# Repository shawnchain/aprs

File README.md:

# TinyAPRS - A cheap APRS TNC for HAM #

### What is TinyAPRS ###

Like most of the APRS TNCs, TinyAPRS is an AFSK1200 modem that decodes radio signals into AX25 data packets. TinyAPRS also supports KISS protocol, so you can use it with most of the APRS applications.

Unlike most of the APRS TNCs, tinyAPRS is VERY VERY CHEAP. It will only cost $10 to build one. That means you can build your own APRS IGATE or tracking beacon with very low cost.

TinyAPRS has good performance on decoding. 
Currently, it works perfectly with my GM300 radio and decodes packets successfully from OT++(The local Digipeater)/FTM350R(My Car) and other devices. Based on my test, it decodes 850+ records from WA8LMF APRS TestCD/Track1. 

### How did it work ###

TinyAPRS is built on the giants shoulder.

 - An ALC/Filter circut that is the same as OpenTracker used, which will  greatly improve the decode capability.(Thank you to BH4TDV for sharing the circut design)
 - A fine-tunned AFSK/AX25/KISS stack that runs on AVR chip with very small memory footprints. (Thank you to Mark Qvist for his MicroAPRS, but mine now is better :)
 - Good abstraction to the hardware with BertOS, which made it easy to port TinyAPRS firmware to other MCUs.

Technical specification 

 - Main Chip : ATMEL/ATMEGA328P (Cheap clones of Arduino ProMini, could be ported to other type of AVR MCUs with ease)
 - ALC circut: MCP6001 OPA
 - Firmware  : AFSK1200/KISS(P-CSMA)/AT Serial

### The License ###

TinyAPRS is released under GPL license, **but with the following restriction** :

 - Any person, who decide to use and/or get benefits from any part of the TinyAPRS project, will be obliged to send the author(me/BG5HHP/Shawn) a gift. (Any kind of gift will be fine but Beers/PostCards/Parts of HAM radios are preferred :)
 - No commercial use.
 - All GPL restrictions

### Pictures ###

Please visit my [weibo album](http://www.weibo.com/p/1005052321043580/album?from=page_100505&mod=TAB#place "Weibo Album") for more pictures.

Cheers,

Shawn (BG5HHP)

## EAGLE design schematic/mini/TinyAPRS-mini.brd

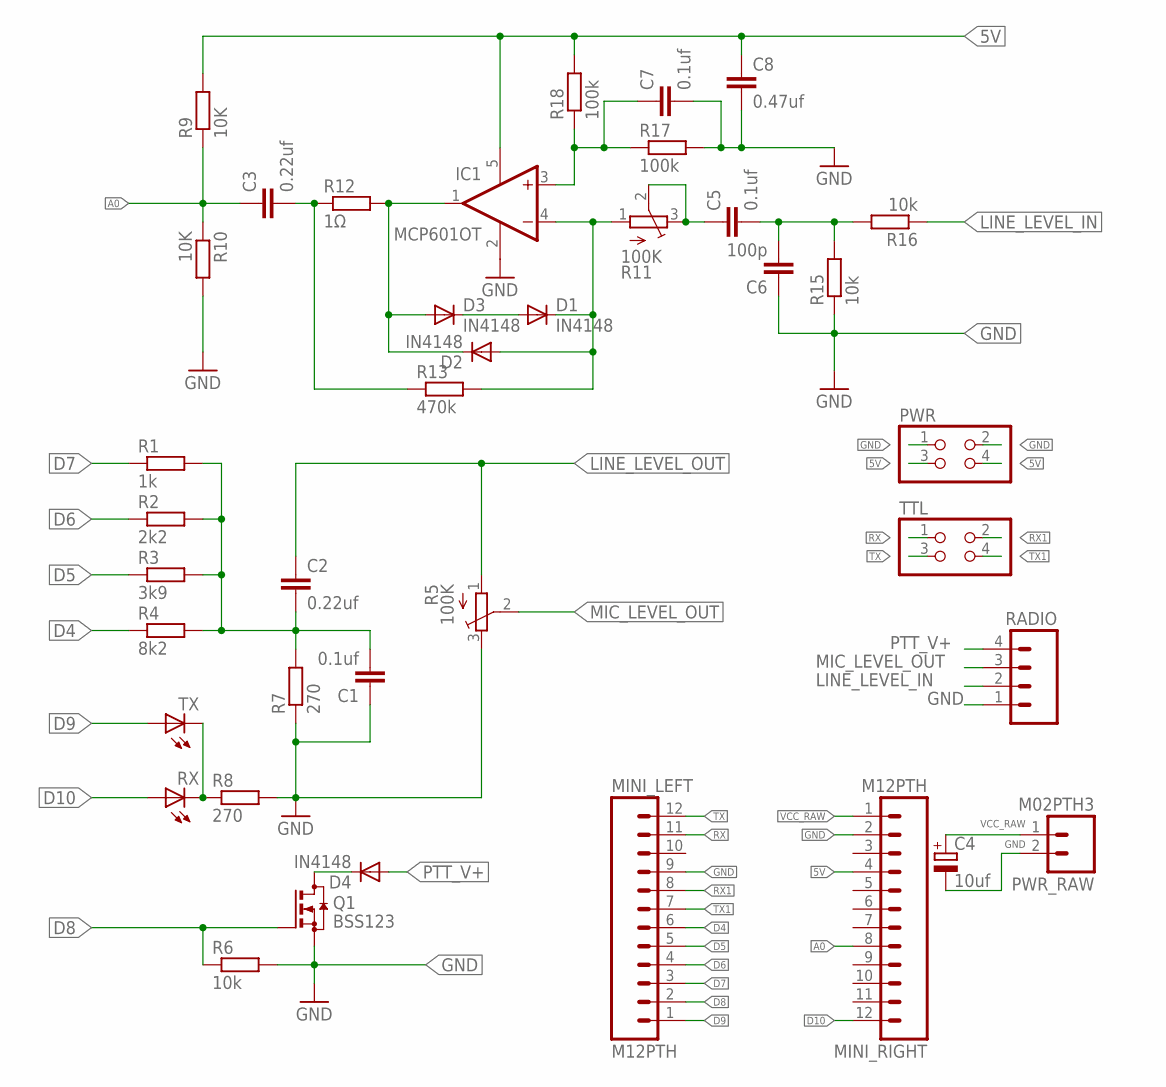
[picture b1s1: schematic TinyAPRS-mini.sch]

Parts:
C1, C5, C7: 0.1uf; C050-024X044
C2, C3: 0.22uf; C050-024X044
C4: 10uf; E2,5-5
C6: 100p; C050-024X044
C8: 0.47uf; C050-024X044
D1, D2, D3, D4: IN4148; D-2.5
IC1: MCP601OT; SOT23-5
MINI_LEFT: M12PTH; 1X12
MINI_RIGHT: M12PTH; 1X12
PWR: PINHD-2X2; 2X02
PWR_RAW: M02PTH3; 1X02_LONGPADS
Q1: BSS123; SOT23
R1: 1k; 0204/5
R2: 2k2; 0204/5
R3: 3k9; 0204/5
R4: 8k2; 0204/5
R5, R11: 100K; TC33X
R6, R15, R16: 10k; 0204/5
R7: 270; 0204/5
R8: 270; 0204V
R9, R10: 10K; 0204/5
R12: 1Ω; 0204V
R13: 470k; 0204/5
R17, R18: 100k; 0204/5
RADIO: M04PTH; 1X04
RX: LED_ELD260; LED_LD260
TTL: PINHD-2X2; 2X02
TX: LED_ELD260; LED_LD260

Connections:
5V: C8.1, IC1.5 (V+), MINI_RIGHT.4, PWR.3, PWR.4, R9.2, R18.2
A0: C3.1, MINI_RIGHT.8, R9.1, R10.1
D4: MINI_LEFT.6, R4.1
D5: MINI_LEFT.5, R3.1
D6: MINI_LEFT.4, R2.1
D7: MINI_LEFT.3, R1.1
D8: MINI_LEFT.2, Q1.1 (G), R6.1
D9: MINI_LEFT.1, TX.A
D10: MINI_RIGHT.12, RX.A
GND: C1.1, C4.-, C6.1, C7.2, C8.2, IC1.2 (V-), MINI_LEFT.9, MINI_RIGHT.2, PWR.1, PWR.2, PWR_RAW.2, Q1.2 (S), R5.3 (E), R6.2, R7.1, R8.2, R10.2, R15.1, R17.2, RADIO.1
LINE_LEVEL_IN: R16.1, RADIO.2
LINE_LEVEL_OUT: C2.1, R5.1 (A)
MIC_LEVEL_OUT: R5.2 (S), RADIO.3
unnamed: R8.1, RX.K (C), TX.K (C)
unnamed: D2.C, D3.A, IC1.1 (OUT), R12.2
unnamed: D1.C, D2.A, IC1.4 (-IN), R11.1 (A), R13.2
unnamed: D4.C, Q1.3 (D)
unnamed: C5.1, R11.2 (S), R11.3 (E)
unnamed: C5.2, C6.2, R15.2, R16.2
unnamed: C7.1, IC1.3 (+IN), R17.1, R18.1
unnamed: D1.A, D3.C
unnamed: C3.2, R12.1, R13.1
PTT_V+: D4.A, RADIO.4
RX: MINI_LEFT.11, TTL.1
RX1: MINI_LEFT.8, TTL.2
R_DAC: C1.2, C2.2, R1.2, R2.2, R3.2, R4.2, R7.2
TX: MINI_LEFT.12, TTL.3
TX1: MINI_LEFT.7, TTL.4
VCC_RAW: C4.+, MINI_RIGHT.1, PWR_RAW.1

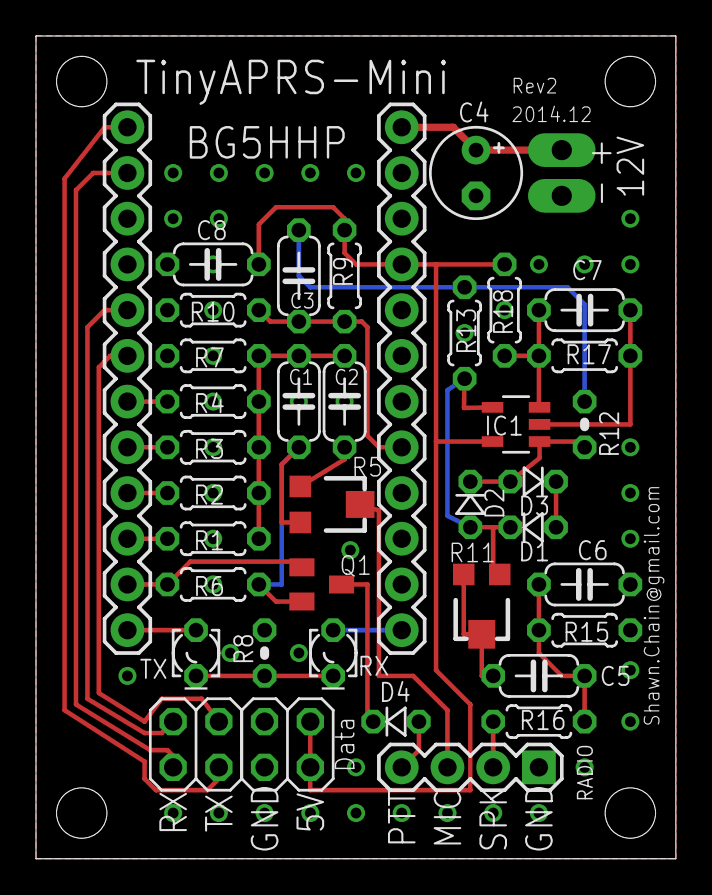
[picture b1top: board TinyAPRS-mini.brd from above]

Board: 2 copper layers, 35.5 x 45.7 mm, 39 parts (0 on the bottom side), 29 nets.

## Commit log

2014-10-11 Add MicroAPRS2 source code
2014-10-13 Updated to use GPIO D8 for PTT, D9,D10 for TX,RX
2014-10-14 Add LCD4884 driver
2014-10-14 Add ATMEGA644PA CPU support to BeRTOS
2014-10-14 Add the missing cpu definition file
2014-10-18 Add HAL macros to LCD drv
2014-10-18 Add External AREF macros to AFSK drv
2014-10-18 Add LCD support to console module
2014-10-18 Console supports LCD
2014-10-21 Add CONFIG_KISS_QUEUE parameter for the kiss protocol
2014-11-25 Add ATMEGA644PA patch
2014-11-25 Add TinyAPRS project file
2014-11-25 Add TinyAPRS project
2015-02-07 Commit pending changes on MicroAPRS2 copy, now will work on TinyAPRS branch
2015-02-07 Add experimental KISS support
2015-02-07 move unchanged cfg headers to templates folder for better reading
2015-02-08 ax25 driver supports pass_through mode.
2015-02-11 disable KISS message queue when CONFIG_KISS_QUEUE=0 to save ram space.
2015-02-11 module configuration update.
2015-02-11 Simple AT command supported for callsign and ssid configuration.
2015-02-11 CSMA before sending even sending queue is disabled.
2015-02-13 Refactored to: extract beacon module; support KISS/COMMAND mode switch
2015-02-13 Kiss module now supports return command
2015-02-14 Increase the premble and trailer time for better decoding performance.
2015-02-14 Add beacon_send_test(uint8_t)
2015-02-14 update callsign and ssid from settings
2015-02-14 Optimize the path in test message.
2015-02-15 Adjust afsk premble and trail time. should be configurable.
2015-02-19 Suports print string from PROGMEM to save runtime ram
2015-02-19 The new console module for AT command support.
2015-02-19 Display free mem after init.
2015-02-20 Refactor KISS module to work with other modules that shares one UART
2015-02-20 Refactored console serial read
2015-02-21 Compatible with OT2/Other KISS enable command.
2015-02-24 Add configuration tool skeleton code
2015-02-28 Add print_size and flash target to the makefile
2015-02-28 Add settings support for MYCALL,DEST,PATH
2015-02-28 respond 'INVALID CMD VALUE' to console when command handler returns false
2015-02-28 Add console test command, use CONSOLE_TEST_COMMAND_ENABLED to enable/disable.
2015-02-28 settings copy call value optimized.
2015-03-01 Refactor the console and commands
2015-03-03 Clean up console commands.
2015-03-03 KISS module optimized.
2015-03-03 Beacon test message bugfix
2015-03-07 soft reboot device after settings are cleared.
2015-03-07 New console command supported: location and comments
2015-03-07 Code clean up on console settings commands
2015-03-07 Help command clean up.
2015-03-07 restore the changes on main.c
2015-03-07 console help command clean up
2015-03-08 don't print ssid 0
2015-03-08 print received ax25 message in TNC2-stye format in normal mode.
2015-03-08 Ready for 1.0-RC
2015-03-15 Add initial soft_serial code
2015-03-15 tesing soft_serial
2015-03-15 Add missing hw_pins_arduino.h
2015-03-15 Disable soft reset by default
2015-03-15 Ready for 1.0
2015-03-15 Remove legacy codes
2015-03-15 README typo fix.
2015-03-15 For my bad english.
2015-03-15 Pictures!
2015-03-15 Update README with pictures.
2015-03-16 Add schematic for the mini board
2015-03-20 Heading for the 1.1
2015-03-20 Add .settings to ignore list
2015-03-20 softser code cleanup
2015-03-25 beacon module optimized.
2015-03-25 Optimized softser for the radio module initialization.
2015-03-25 radio modules is disabled by default on 328p
2015-03-25 rename utils module.
2015-03-25 code clean up
2015-03-25 Supports raw packet in settings, but disabled by default.
2015-03-25 console serial buf down to 32bytes if raw packet is disabled in settings to save sram space
2015-03-25 Remove PHGD/LOCATION/COMMENTS from settings.
2015-03-25 AT command parser bugfix
2015-03-25 Symbol in settings.
2015-03-25 symbol table and index support.
2015-03-26 beacon now reads the settings for raw aprs data
2015-03-26 reduce the afsk premble time to 350ms
2015-03-27 add doc folder
2015-03-27 Update doc
2015-03-27 Add gps nmea parser
2015-03-27 Add gps callback
2015-03-29 Extract the read_a_line logic into the reader class.
    Configure the serial in non-blocking mode by setting
    CONFIG_SER_RXTIMEOUT = 0
2015-03-29 Extract serial instance to global.
2015-03-29 Extract g_afsk & g_ax25 instances to global.
    KISS module now uses kfile_getc to read a char from serial, instead of
    the deprecated ser_getchar_nowait() call.
2015-03-29 Extract gps to global
2015-03-29 Rename NMEA to GPS
2015-03-30 gps module refactored
2015-03-30 modify ax25 to print message count when CONFIG_AX25_DEBUG_PRINT_MESSAGE_COUNT = 1
2015-03-30 supports tracker mode. currently use AT+MODE=2 to enable
2015-03-31 Beacon module refers GPS module directly.
2015-03-31 run_mode now will be saved to settings and device automatically enter even after reboot.
2015-03-31 beacon supports GPS tracking.
2015-03-31 check_run_mode bugfix in main loop
2015-03-31 cmd_help() text refined.
2015-03-31 always trigger send when first time gps location arrived.
2015-04-01 smart beacon
2015-04-01 always set gps baudrate to 9600
2015-04-01 beacon dst callsign bugfix
2015-04-01 dont pause when dumping beacon payload
2015-04-01 GPS initialize sequence optimized.
2015-04-02 increase the wait time of each gps init command
2015-04-02 Bugfix on GPS receiving.
2015-04-03 GPS works
2015-04-05 Bugfix on ax25_print() that missing message
2015-04-05 light on gps indicator LED inside gps mdoule.
2015-04-07 remove unused fields in struct Reader to save ram.
2015-04-07 KISS and CONSOLE now shares the same read buffer which will save 330 bytes of sram.
2015-04-07 KISS uses global afsk & ax25 handlers.
2015-04-07 Use CONFIG_AX25_FRAME_BUF_LEN as shared buffer length
2015-04-09 Collecting ax25 protocol statistic info.
2015-04-09 rename the beacon text in settings and changes the AT+TEXT, AT+CALL commands.
2015-04-09 Extract free_mem() into utils, which returns the free mem might be slightly smaller than the actuall one(2 bytes maybe) but fine.
2015-04-09 reader code clean up
2015-04-09 add BEACON_INTERVAL to settings
2015-04-09 Use AT+BEACON=45 to setup beacon broadcast interval.
2015-04-09 works with latest refactors.
2015-04-10 gps_get_location() now converts lat/lon in to decimal number from degress string. and other minor fixes on GPS modules.
2015-04-10 smart beacon implemented. simplified beacon test code.
2015-04-10 work with latest changes.
2015-04-10 GPS supports GPGGA sentence.
2015-04-10 convert altitude to feet for APRS payload.
2015-04-10 Fixed the GPS bug that failed to parse timestamp.
2015-04-11 Fix incorrect altitude in beacon comments.
2015-04-13 smartbeacon heading check bugfix.
2015-04-13 Bugfix that beacon send failure if text is blank.
2015-04-13 ax25 layer supports ax25_sendMsg() for digipeater.
2015-04-13 Implemented Digipeater mode.
2015-04-13 force delay 250ms for each repeat
2015-04-13 improved smartbeacon don't send when stopped.
2015-04-14 smartbeacon optimized.
2015-04-14 Digi support message duplication check. by default dup-check interval is 15s
2015-04-14 remove debug printf in digi module.
2015-04-14 check duplicated dst/src for digirepeating message
2015-05-01 bug fixed on smart beacon angel calculation
2015-05-01 rename beacon type in settings.
2015-05-01 diig code review and clean up. seems all fine now.
2015-05-02 Direct load/save call from EEPROM instead of from SRAM which saves 24 bytes of memory.
2016-08-28 Refine the help command as per issue #5 described
2016-09-24 digipeater bug fix
2016-10-05 Add SM50 Howto images
2016-10-05 Add pin setup image
2016-10-06 Add SM50 TX setup images
2016-10-06 Update tx setup images
2016-10-08 Add H618B Howto
2016-10-08 Update H618B Images
2016-10-08 Optimized Makefile to support modules
2016-10-08 Update main
2016-10-08 Extract GPS Tracker module
2016-10-10 uart drv optimized
2016-10-11 commit the test code for hdlc/afsk refactoring
2016-10-12 I2C porting WIP
2016-10-12 Upgrade bertos drivers to g8ecj's bertos fork
2016-10-12 issue #1 optimized the kfile_printf_P() to save 120 bytes of sram
2016-10-13 Kiss module optimized
2016-10-13 digi module includes the counter, optimize the printf_P call
2016-10-13 optimize kiss csma send
2016-10-13 flush the afsk layer after an ax25 msg is sent
2016-10-13 bugfix
2016-10-13 Serial port default baudrate increased to 115200
2016-10-14 Add kiss config command and save received bytes into config eeprom
2016-10-16 Update bootloader hex
2016-10-17 Add bootloader source patches
2016-10-17 Update bootloader makefile and conf
2016-10-17 Clean up build files
2016-10-17 Update bootloader with PROGRAM_MODE support
2016-10-17 Using watchdog for reboot
2016-10-17 add wdt_init() to avoid infinite loop for NO_BOOTLOADER case
2016-10-19 Fold the beacon parameters in settings
2016-10-20 code cleanup on settings module
2016-10-20 Optimize console code
2016-10-20 Extract serial readline logic into SerialReader
2016-10-21 Refactored GPS/Tracker modules
2016-10-21 Support write into settings via KISS protocol
2016-10-22 Update kiss settings handling
2016-10-23 Refactored the CALL data settings
2016-10-23 Work with settings changes
2016-10-23 KISS module works with settings changes
2016-10-23 Update the magic config commands
2016-10-23 display welcome banner when started
2016-10-24 optimized the kiss config protocol
2016-10-26 Add crc field in kiss/settings response frame
2016-10-26 Add version support
2016-11-04 kiss mode by default
2016-11-04 remove commit settings cmd
2016-11-04 Update bootloader signature
2016-11-04 Fixed compile broken issue
2017-01-16 beacon auto broadcast bugfix
2017-01-30 reset serial after baudrate changes.
2017-01-30 nothing changed
2017-02-03 merged bugfix 5e53f91
2017-02-04 Correct the NRZ-S coding in AFSK, which is used by APRS/HDLC/BELL202. Fixes the IIR filter cutoff frequency to about 1200HZ
2017-02-04 by default disable carrier detect flag in AFSK
2017-02-04 Minor changes on filter cutoff frequency
2017-03-14 1.1.0
2017-03-14 Heading for 1.2
2017-07-18 Update DST call to APTA
2017-07-18 Bump version to 1.1.1
2017-08-02 The radio board support
2017-08-02 refine arduino pin headers
2018-06-13 Update device TOCALL to APTBxx assigned by WB4APR

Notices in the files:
parts and their libraries:
SparkFun-Connectors: Licensing: Creative Commons ShareAlike 4.0 International - https://creativecommons.org/licenses/by-sa/4.0
